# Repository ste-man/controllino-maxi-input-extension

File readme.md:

# Controllino MAXI Input Extension

A small DIN-rail mounted add-on board that adds **four 24 V inputs** to a
[CONTROLLINO MAXI](https://www.controllino.com/) PLC. The board plugs into the PLC's
**X2 pin header** with a 26-pin ribbon cable. It scales 24 V field signals down to
the 0–5 V range of the analog inputs **A10–A13** on that header, and has an indicator
LED for each channel.

## Features

- 4 input channels (A10, A11, A12, A13) for 24 V DC signals
- Resistor divider (47 kΩ / 10 kΩ) scales 24 V to about 4.2 V for the PLC's ADC
- 100 nF RC low-pass filter on each channel to reduce noise
- Green status LED per channel, driven by a 74LS125 buffer so the LEDs do not load the measured signal
- Blue LED for Controllino +5 V power supply
- Powered from the PLC: +5 V and GND come over the ribbon cable, so no external supply is needed
- WAGO push-in terminal block for field wiring
- Fits an [Italtronic XT72](https://eng.italtronic.com/products/support_xt_en/xt_72_support_xt_en/) DIN-rail PCB holder (board size 31.05 × 72.15 mm)

## Photos

| PCB render | Board and DIN-rail holder |
|---|---|
|  |  |

## How it works

1. **Voltage divider.** A 47 kΩ / 10 kΩ divider scales the input by 10 / 57 ≈ 0.175.
2. **Filter.** A 100 nF capacitor across the 10 kΩ resistor forms a low-pass filter
   with a cut-off frequency of about 190 Hz (source impedance 47 k ∥ 10 k ≈ 8.2 kΩ).
3. **To the PLC.** The divided voltage goes straight to the matching analog pin on the
   ribbon cable, where the PLC reads it.
4. **Indicator.** The same signal also feeds one gate of a 74LS125 quad buffer, whose
   output drives the channel's LED through a 1 kΩ resistor. The output-enable pins
   are tied to GND, so all four buffers are always on.

### Signal levels (ideal divider)

| Input voltage | Voltage at PLC pin | 10-bit ADC reading (5 V ref) |
|---:|---:|---:|
| 0 V | 0 V | 0 |
| 17.1 V | 3.00 V | ~614 |
| 24 V | 4.21 V | ~862 |
| 28.5 V | 5.00 V | 1023 (full scale) |

Comment: Minimum Voltage for ATMEGA2560 (Controllino Maxi CPU) input to be considered High is 0.6×VCC (see ATMEGA2560 datasheet). 0.6×5.0 V(VCC) = 3.0 VDC

Input current at 24 V is ~0.42 mA per channel.

> **Note:** These figures assume an ideal divider. The 74LS125 input current loads
> the divider slightly, so check the actual readings on your hardware and set your
> software thresholds from those. Keep the inputs below about 28 V so the PLC pin
> stays within its 5 V range.

## Bill of materials

Recommended component manufacturer and part numbers are attached to KiCad schematic symbol properties. See image of symbol properties table below:

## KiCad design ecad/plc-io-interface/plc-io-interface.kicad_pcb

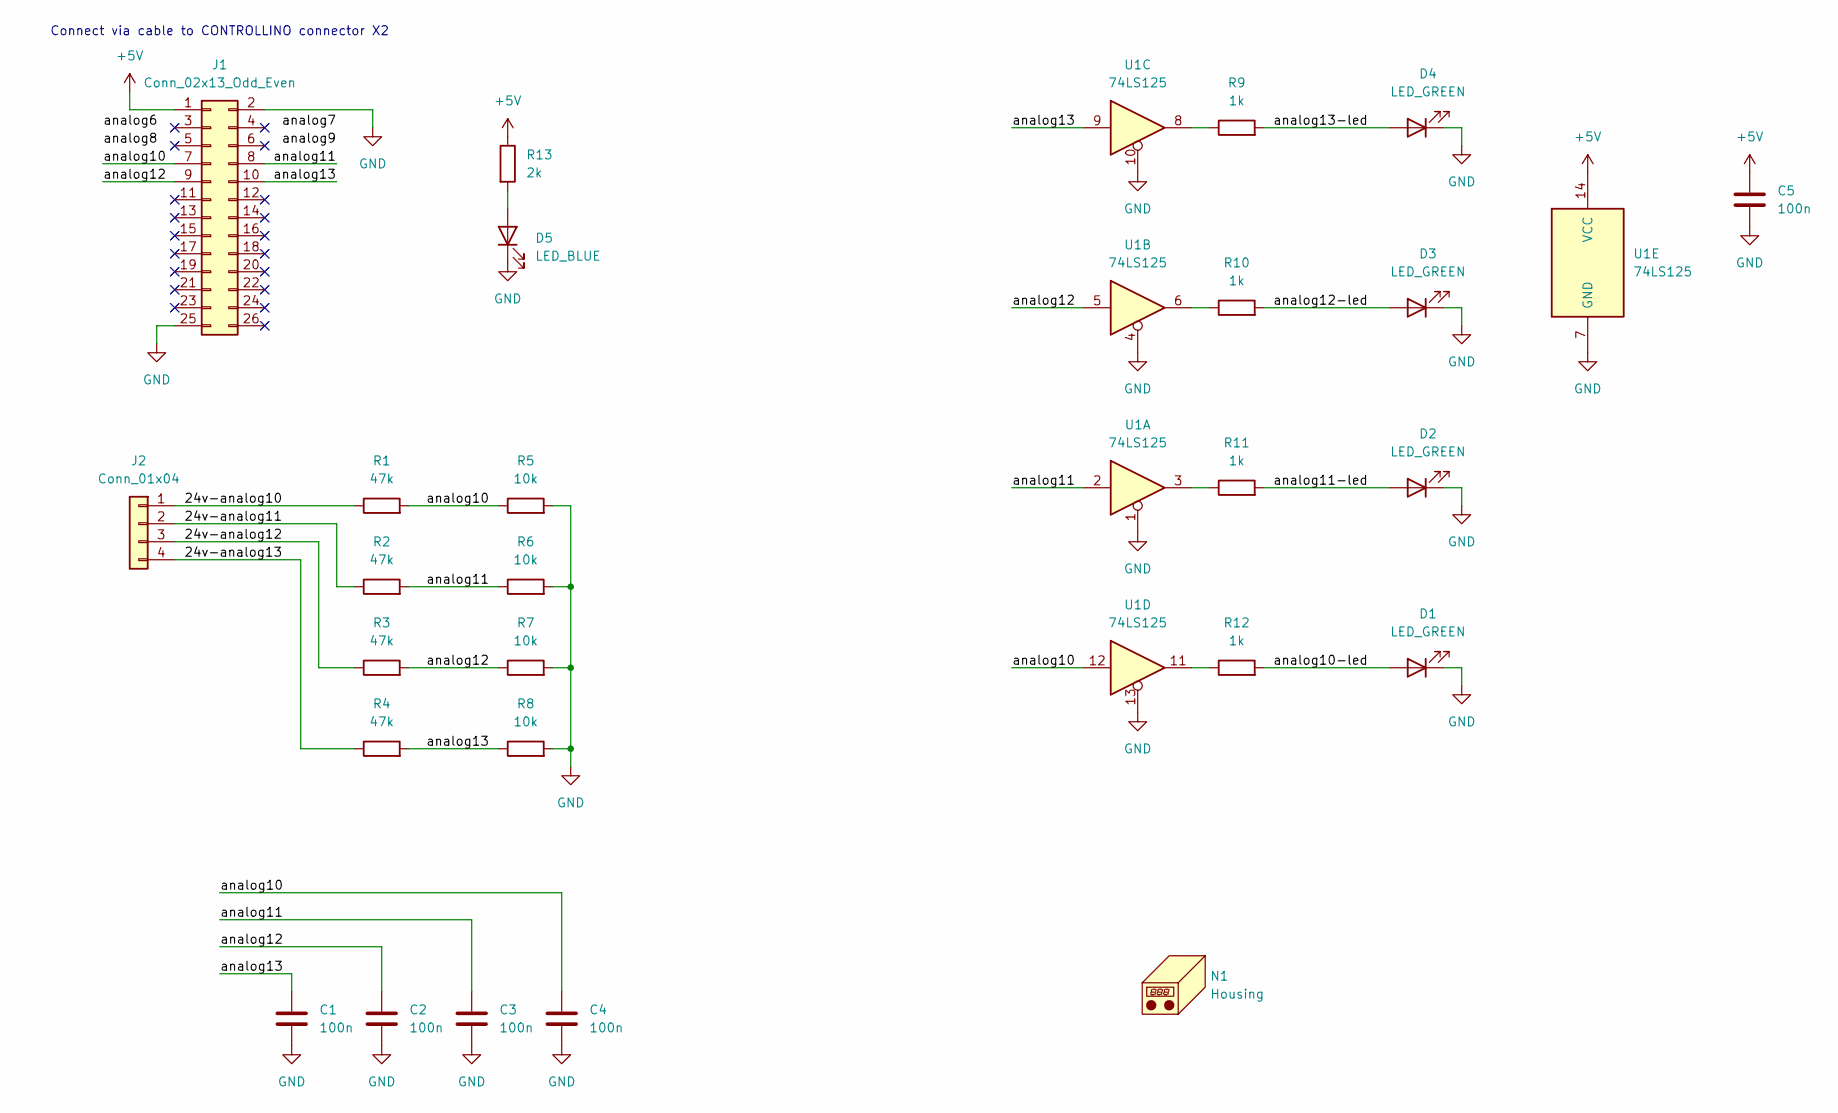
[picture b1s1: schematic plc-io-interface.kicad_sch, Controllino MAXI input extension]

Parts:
C1, C2, C3, C4, C5: 100n; C_0805_2012Metric_Pad1.18x1.45mm_HandSolder; LCSC Part # C49678
D1, D2, D3, D4: LED_GREEN; LED_0805_2012Metric_Pad1.15x1.40mm_HandSolder; LCSC Part # EVALUATE!!
D5: LED_BLUE; LED_0805_2012Metric_Pad1.15x1.40mm_HandSolder; Digikey part number 3147-B1701NB--20D000114U1930
J1: Conn_02x13_Odd_Even; IDC-Header_2x13_P2.54mm_Vertical
J2: Conn_01x04; wago-2086-3104; Digikey part number 2946-2086-3104-ND
N1: Housing
R1, R2, R3, R4: 47k; R_1206_3216Metric
R5, R6, R7, R8: 10k; R_0805_2012Metric_Pad1.20x1.40mm_HandSolder; LCSC Part # C17414
R9, R10, R11, R12: 1k; R_0805_2012Metric_Pad1.20x1.40mm_HandSolder; Digikey part number YAG3703CT-ND
R13: 2k; R_0805_2012Metric_Pad1.20x1.40mm_HandSolder; LCSC Part # C17604
U1: 74LS125; SO-14_3.9x8.65mm_P1.27mm

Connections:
+5V: C5.1, J1.1, R13.1, U1.14 (VCC)
/24v-analog10: J2.1, R1.1
/24v-analog11: J2.2, R2.1
/24v-analog12: J2.3, R3.1
/24v-analog13: J2.4, R4.1
/analog10: C4.1, J1.7, R1.2, R5.1, U1.12
/analog10-led: D1.2 (A), R12.2
/analog11: C3.1, J1.8, R2.2, R6.1, U1.2
/analog11-led: D2.2 (A), R11.2
/analog12: C2.1, J1.9, R3.2, R7.1, U1.5
/analog12-led: D3.2 (A), R10.2
/analog13: C1.1, J1.10, R4.2, R8.1, U1.9
/analog13-led: D4.2 (A), R9.2
GND: C1.2, C2.2, C3.2, C4.2, C5.2, D1.1 (K), D2.1 (K), D3.1 (K), D4.1 (K), D5.1 (K), J1.2, J1.25, R5.2, R6.2, R7.2, R8.2, U1.1, U1.4, U1.7 (GND), U1.10, U1.13
unnamed: D5.2 (A), R13.2
unnamed: R9.1, U1.8
unnamed: R10.1, U1.6
unnamed: R11.1, U1.3
unnamed: R12.1, U1.11

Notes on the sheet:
Connect via cable to CONTROLLINO connector X2

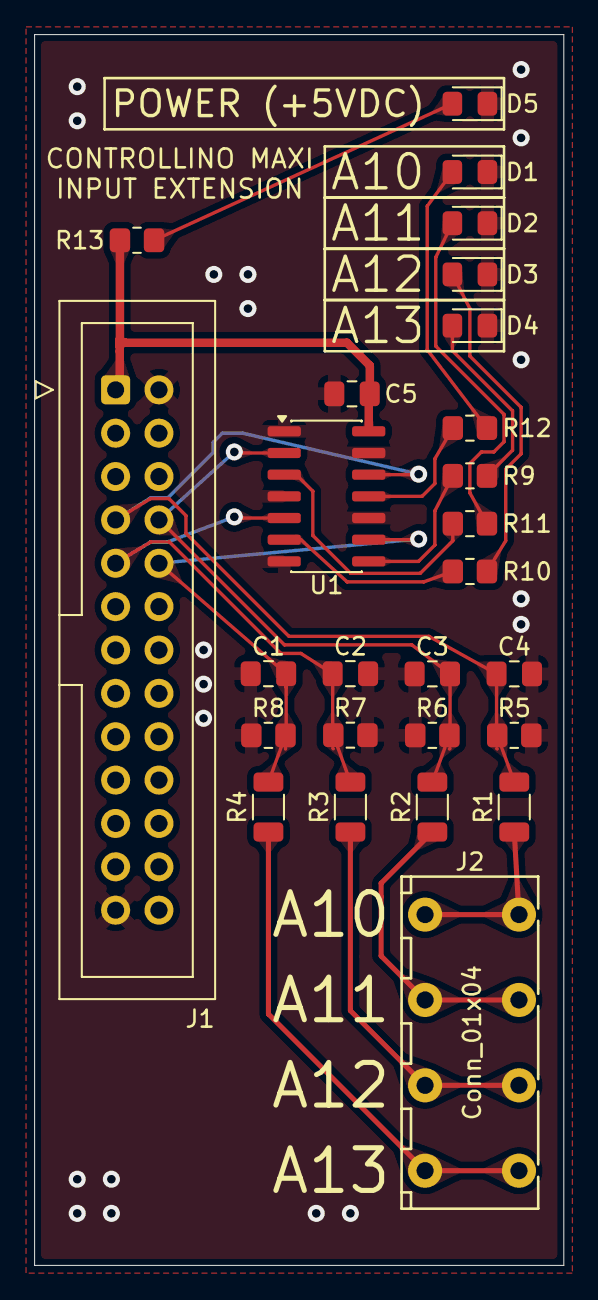
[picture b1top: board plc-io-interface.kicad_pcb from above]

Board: 2 copper layers, 31.0 x 72.1 mm, 26 parts (0 on the bottom side), 19 nets.
